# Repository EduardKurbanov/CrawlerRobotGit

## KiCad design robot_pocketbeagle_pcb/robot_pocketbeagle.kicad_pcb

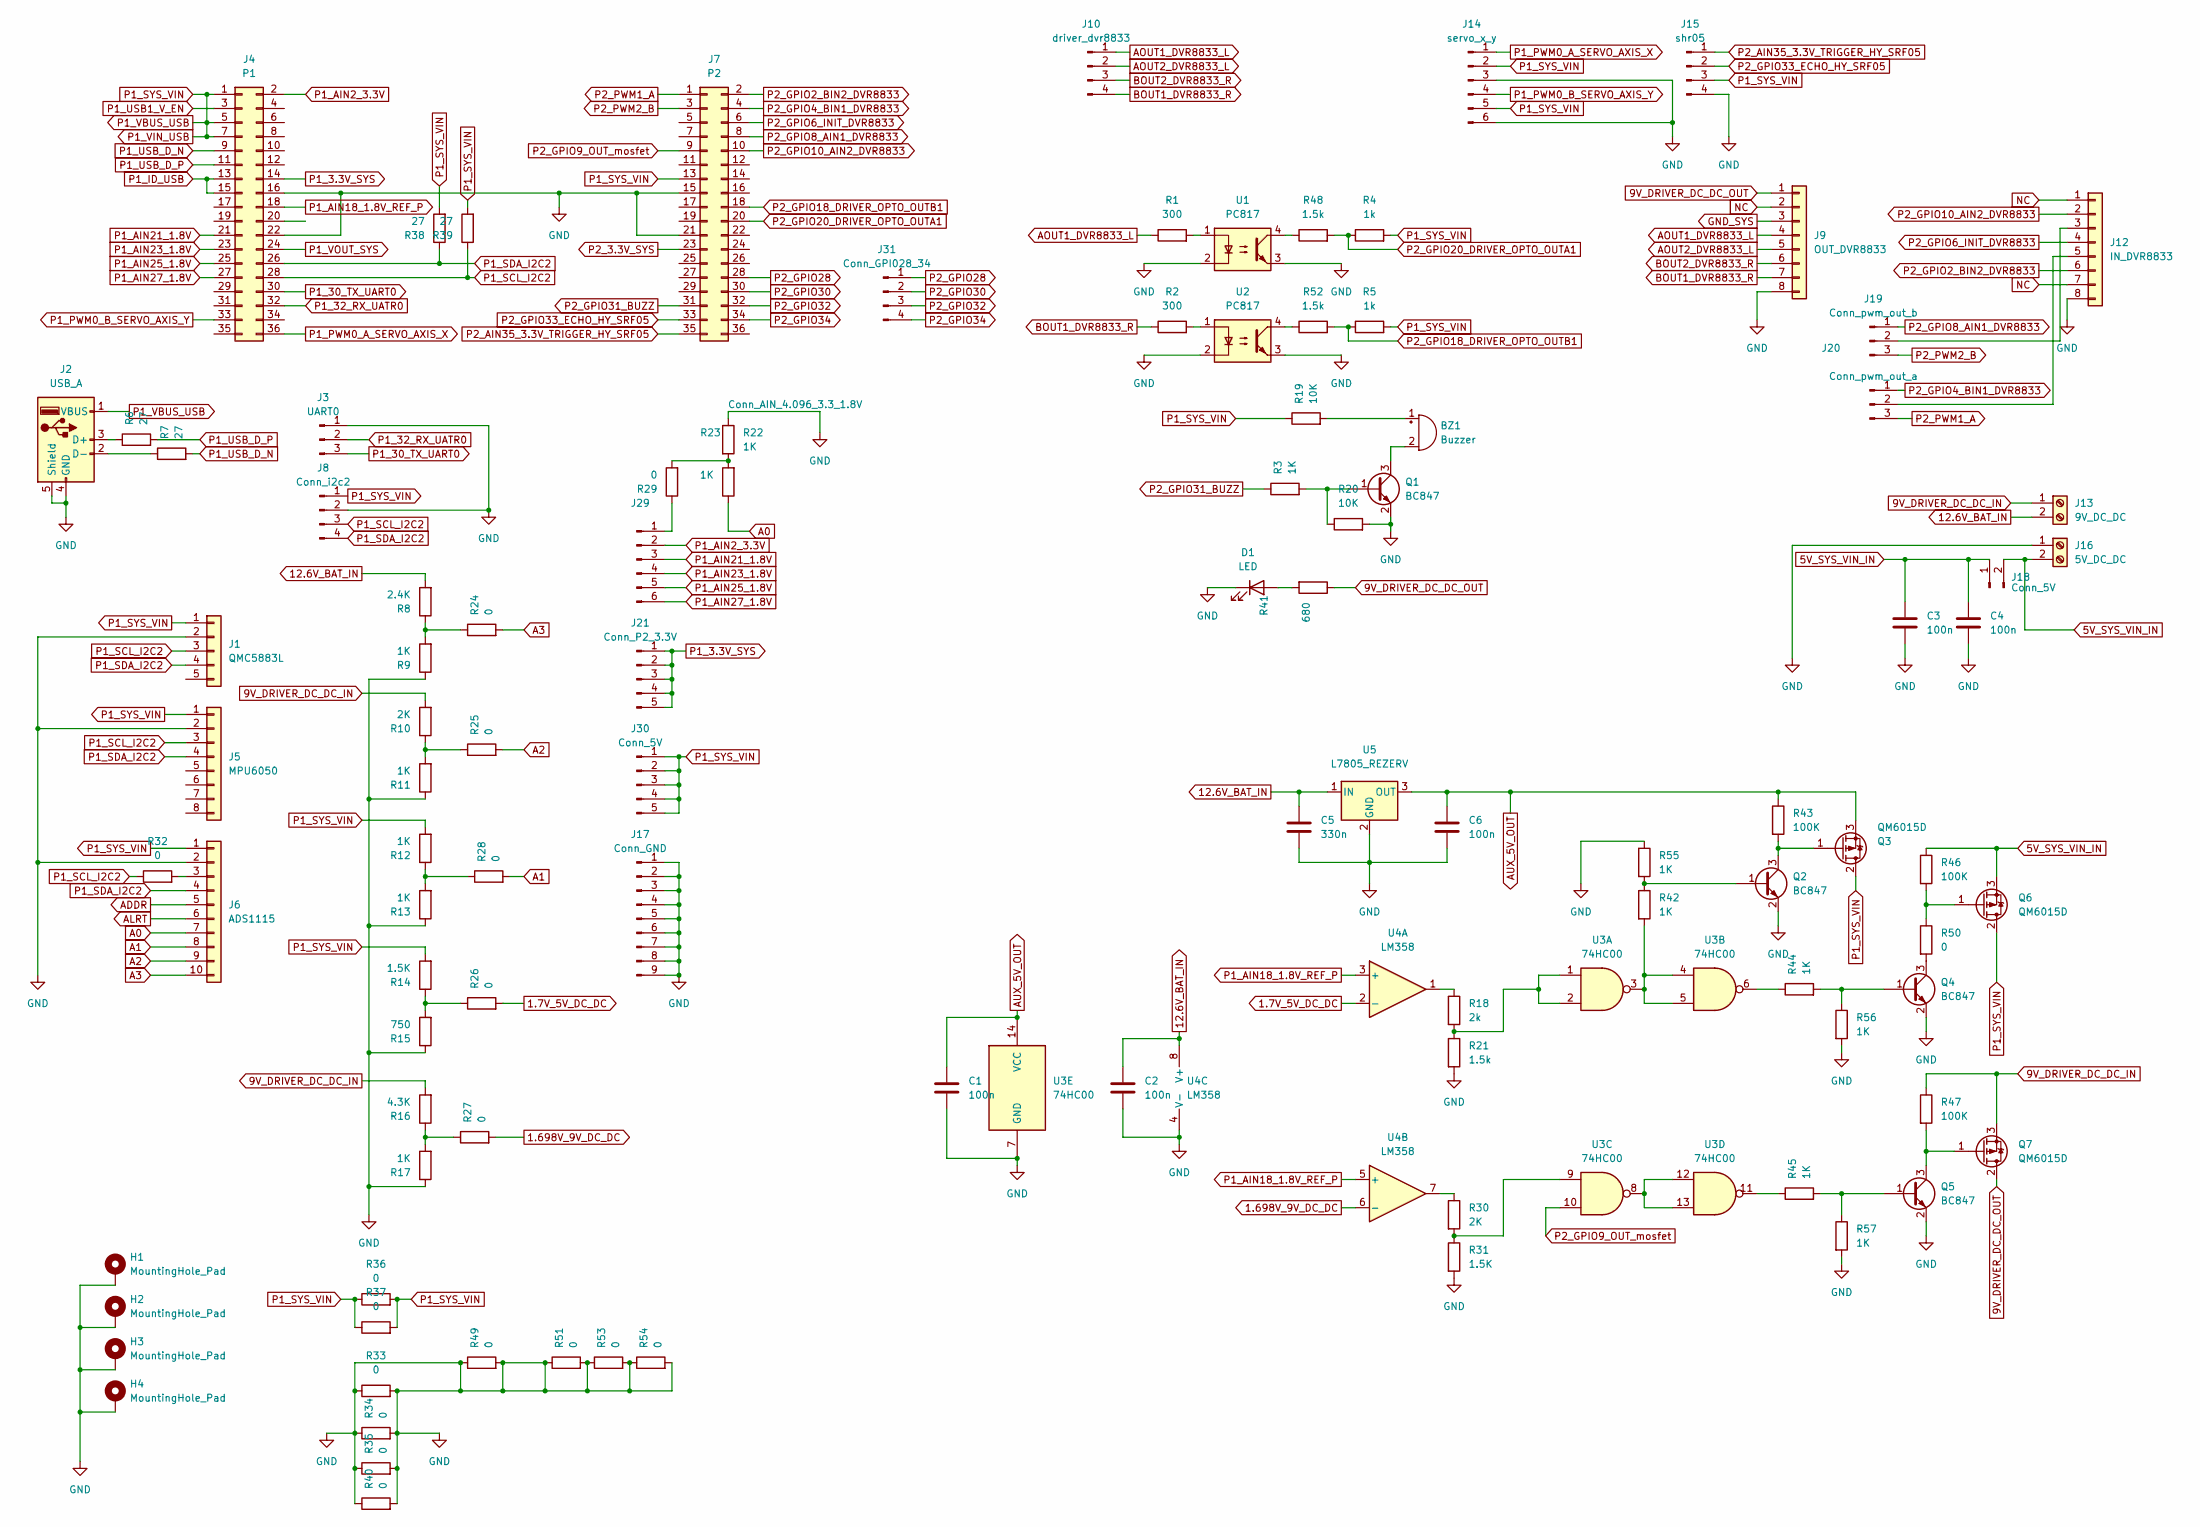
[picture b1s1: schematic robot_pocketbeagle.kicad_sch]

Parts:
BZ1: Buzzer; Buzzer_12x9.5RM7.6
C1, C2, C3, C4, C6: 100n; C_0805_2012Metric
C5: 330n; C_0805_2012Metric
D1: LED; LED_D3.0mm
H1, H2, H3, H4: MountingHole_Pad; MountingHole_3.2mm_M3_DIN965_Pad_TopBottom
J1: QMC5883L; PinSocket_1x05_P2.54mm_Vertical
J2: USB_A; USB_A_CONNFLY_DS1095-WNR0
J3: UART0; PinHeader_1x03_P2.54mm_Vertical
J4: P1; PinHeader_2x18_P2.54mm_Vertical
J5: MPU6050; PinHeader_1x08_P2.54mm_Vertical
J6: ADS1115; PinHeader_1x10_P2.54mm_Vertical
J7: P2; PinHeader_2x18_P2.54mm_Vertical
J8: Conn_i2c2; PinSocket_1x04_P2.54mm_Vertical
J9: OUT_DVR8833; PinSocket_1x08_P2.54mm_Vertical
J10: driver_dvr8833; PinHeader_1x04_P2.54mm_Vertical
J12: IN_DVR8833; PinSocket_1x08_P2.54mm_Vertical
J13: 9V_DC_DC; TerminalBlock_bornier-2_P5.08mm
J14: servo_x_y; PinHeader_1x06_P2.54mm_Vertical
J15: shr05; PinHeader_1x04_P2.54mm_Vertical
J16: 5V_DC_DC; TerminalBlock_bornier-2_P5.08mm
J17: Conn_GND; PinSocket_1x09_P2.54mm_Vertical
J18: Conn_5V; PinSocket_1x02_P2.54mm_Vertical
J19: Conn_pwm_out_b; PinSocket_1x03_P2.54mm_Vertical
J20: Conn_pwm_out_a; PinSocket_1x03_P2.54mm_Vertical
J21: Conn_P2_3.3V; PinSocket_1x05_P2.54mm_Vertical
J29: Conn_AIN_4.096_3.3_1.8V; PinSocket_1x06_P2.54mm_Vertical
J30: Conn_5V; PinSocket_1x05_P2.54mm_Vertical
J31: Conn_GPI028_34; PinSocket_1x04_P2.54mm_Vertical
Q1, Q2, Q4, Q5: BC847; SOT-23
Q3, Q6, Q7: QM6015D; TO-252-2
R1, R2: 300; R_0805_2012Metric
R3, R9, R11, R12, R13, R17, R22, R23, R42, R44, R45, R55, R56, R57: 1K; R_0805_2012Metric
R4, R5: 1k; R_0805_2012Metric
R6, R7, R38, R39: 27; R_0805_2012Metric
R8: 2.4K; R_0805_2012Metric
R10, R30: 2K; R_0805_2012Metric
R14, R31: 1.5K; R_0805_2012Metric
R15: 750; R_0805_2012Metric
R16: 4.3K; R_0805_2012Metric
R18: 2k; R_0805_2012Metric
R19, R20: 10K; R_0805_2012Metric
R21, R48, R52: 1.5k; R_0805_2012Metric
R24, R25, R26, R27, R28, R29, R49, R51: 0; R_0805_2012Metric
R32, R33, R34, R35, R36, R37, R40, R50, R53, R54: 0; R_1206_3216Metric
R41: 680; R_0805_2012Metric
R43, R46, R47: 100K; R_0805_2012Metric
U1, U2: PC817; DIP-4_W7.62mm
U3: 74HC00; SO-14_3.9x8.65mm_P1.27mm
U4: LM358; SO-8_3.9x4.9mm_P1.27mm
U5: L7805_REZERV; TO-252-2

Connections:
1.7V_5V_DC_DC: R26.2, U4.2 (-)
1.698V_9V_DC_DC: R27.2, U4.6 (-)
5V_SYS_VIN_IN: C3.1, C4.1, J16.2, J18.1, J18.2, Q6.3 (S), R46.1
9V_DRIVER_DC_DC_IN: J13.1, Q7.3 (S), R10.2, R16.2, R47.1
9V_DRIVER_DC_DC_OUT: J9.1, Q7.2 (D), R41.1
12.6V_BAT_IN: C2.1, C5.1, J13.2, R8.2, U4.8 (V+), U5.1 (IN)
A0: J6.7, R23.1
A1: J6.8, R28.2
A2: J6.9, R25.2
A3: J6.10, R24.2
ADDR: J6.5
ALRT: J6.6
AOUT1_DVR8833_L: J9.4, J10.1, R1.1
AOUT2_DVR8833_L: J9.5, J10.2
AUX_5V_OUT: C1.1, C6.1, Q3.3 (S), R43.1, U3.14 (VCC), U5.3 (OUT)
BOUT1_DVR8833_R: J9.7, J10.4, R2.1
BOUT2_DVR8833_R: J9.6, J10.3
GND: C1.2, C2.2, C3.2, C4.2, C5.2, C6.2, D1.1 (K), H1.1, H2.1, H3.1, H4.1, J1.2, J2.4 (GND), J2.5 (Shield), J3.1, J4.16, J4.22, J5.2, J6.2, J7.15, J7.21, J8.2, J9.8, J12.8, J14.3, J14.6, J15.4, J16.1, J17.1, J17.2, J17.3, J17.4, J17.5, J17.6, J17.7, J17.8, J17.9, Q1.2 (E), Q2.2 (E), Q4.2 (E), Q5.2 (E), R9.1, R11.1, R13.1, R15.1, R17.1, R20.2, R21.2, R22.1, R31.2, R33.1, R33.2, R34.1, R34.2, R35.1, R35.2, R40.1, R40.2, R49.1, R49.2, R51.1, R51.2, R53.1, R53.2, R54.1, R54.2, R55.1, R56.2, R57.2, U1.2, U1.3, U2.2, U2.3, U3.7 (GND), U4.4 (V-), U5.2 (GND)
GND_SYS: J9.3
NC: J9.2, J12.1, J12.7
unnamed: BZ1.1 (-), R19.2
unnamed: BZ1.2 (+), Q1.3 (C)
unnamed: D1.2 (A), R41.2
unnamed: J2.2 (D-), R7.1
unnamed: J2.3 (D+), R6.1
unnamed: J6.3, R32.2
unnamed: J12.3, J19.2
unnamed: J12.5, J20.2
unnamed: J29.1, R29.1
unnamed: Q1.1 (B), R3.2, R20.1
unnamed: Q2.1 (B), R42.1, R55.2
unnamed: Q2.3 (C), Q3.1 (G), R43.2
unnamed: Q4.1 (B), R44.2, R56.1
unnamed: Q4.3 (C), R50.2
unnamed: Q5.1 (B), R45.2, R57.1
unnamed: Q5.3 (C), Q7.1 (G), R47.2
unnamed: Q6.1 (G), R46.2, R50.1
unnamed: R1.2, U1.1
unnamed: R2.2, U2.1
unnamed: R10.1, R11.2, R25.1
unnamed: R12.1, R13.2, R28.1
unnamed: R14.1, R15.2, R26.1
unnamed: R16.1, R17.2, R27.1
unnamed: R18.1, U4.1
unnamed: R18.2, R21.1, U3.1, U3.2
unnamed: R22.2, R23.2, R29.2
unnamed: R8.1, R9.2, R24.1
unnamed: R30.1, U4.7
unnamed: R30.2, R31.1, U3.9
unnamed: R42.2, U3.3, U3.4, U3.5
unnamed: R44.1, U3.6
unnamed: R45.1, U3.11
unnamed: R48.1, U1.4
unnamed: R52.1, U2.4
unnamed: U3.8, U3.12, U3.13
P1_3.3V_SYS: J4.14, J21.1, J21.2, J21.3, J21.4, J21.5
P1_30_TX_UART0: J3.3, J4.30
P1_32_RX_UATR0: J3.2, J4.32
P1_AIN2_3.3V: J4.2, J29.2
P1_AIN18_1.8V_REF_P: J4.18, U4.3 (+), U4.5 (+)
P1_AIN21_1.8V: J4.21, J29.3
P1_AIN23_1.8V: J4.23, J29.4
P1_AIN25_1.8V: J4.25, J29.5
P1_AIN27_1.8V: J4.27, J29.6
P1_ID_USB: J4.13, J4.15
P1_PWM0_A_SERVO_AXIS_X: J4.36, J14.1
P1_PWM0_B_SERVO_AXIS_Y: J4.33, J14.4
P1_SCL_I2C2: J1.3, J4.28, J5.3, J8.3, R32.1, R39.1
P1_SDA_I2C2: J1.4, J4.26, J5.4, J6.4, J8.4, R38.1
P1_SYS_VIN: J1.1, J2.1 (VBUS), J4.1, J4.5, J4.7, J5.1, J6.1, J7.13, J8.1, J14.2, J14.5, J15.3, J30.1, J30.2, J30.3, J30.4, J30.5, Q3.2 (D), Q6.2 (D), R4.2, R5.2, R12.2, R14.2, R19.1, R36.1, R36.2, R37.1, R37.2, R38.2, R39.2
P1_USB1_V_EN: J4.3
P1_USB_D_N: J4.9, R7.2
P1_USB_D_P: J4.11, R6.2
P1_VOUT_SYS: J4.24
P2_3.3V_SYS: J7.23
P2_AIN35_3.3V_TRIGGER_HY_SRF05: J7.35, J15.1
P2_GPIO2_BIN2_DVR8833: J7.2, J12.6
P2_GPIO4_BIN1_DVR8833: J7.4, J20.1
P2_GPIO6_INIT_DVR8833: J7.6, J12.4
P2_GPIO8_AIN1_DVR8833: J7.8, J19.1
P2_GPIO9_OUT_mosfet: J7.9, U3.10
P2_GPIO10_AIN2_DVR8833: J7.10, J12.2
P2_GPIO18_DRIVER_OPTO_OUTB1: J7.18, R5.1, R52.2
P2_GPIO20_DRIVER_OPTO_OUTA1: J7.20, R4.1, R48.2
P2_GPIO28: J7.28, J31.1
P2_GPIO30: J7.30, J31.2
P2_GPIO31_BUZZ: J7.31, R3.1
P2_GPIO32: J7.32, J31.3
P2_GPIO33_ECHO_HY_SRF05: J7.33, J15.2
P2_GPIO34: J7.34, J31.4
P2_PWM1_A: J7.1, J20.3
P2_PWM2_B: J7.3, J19.3

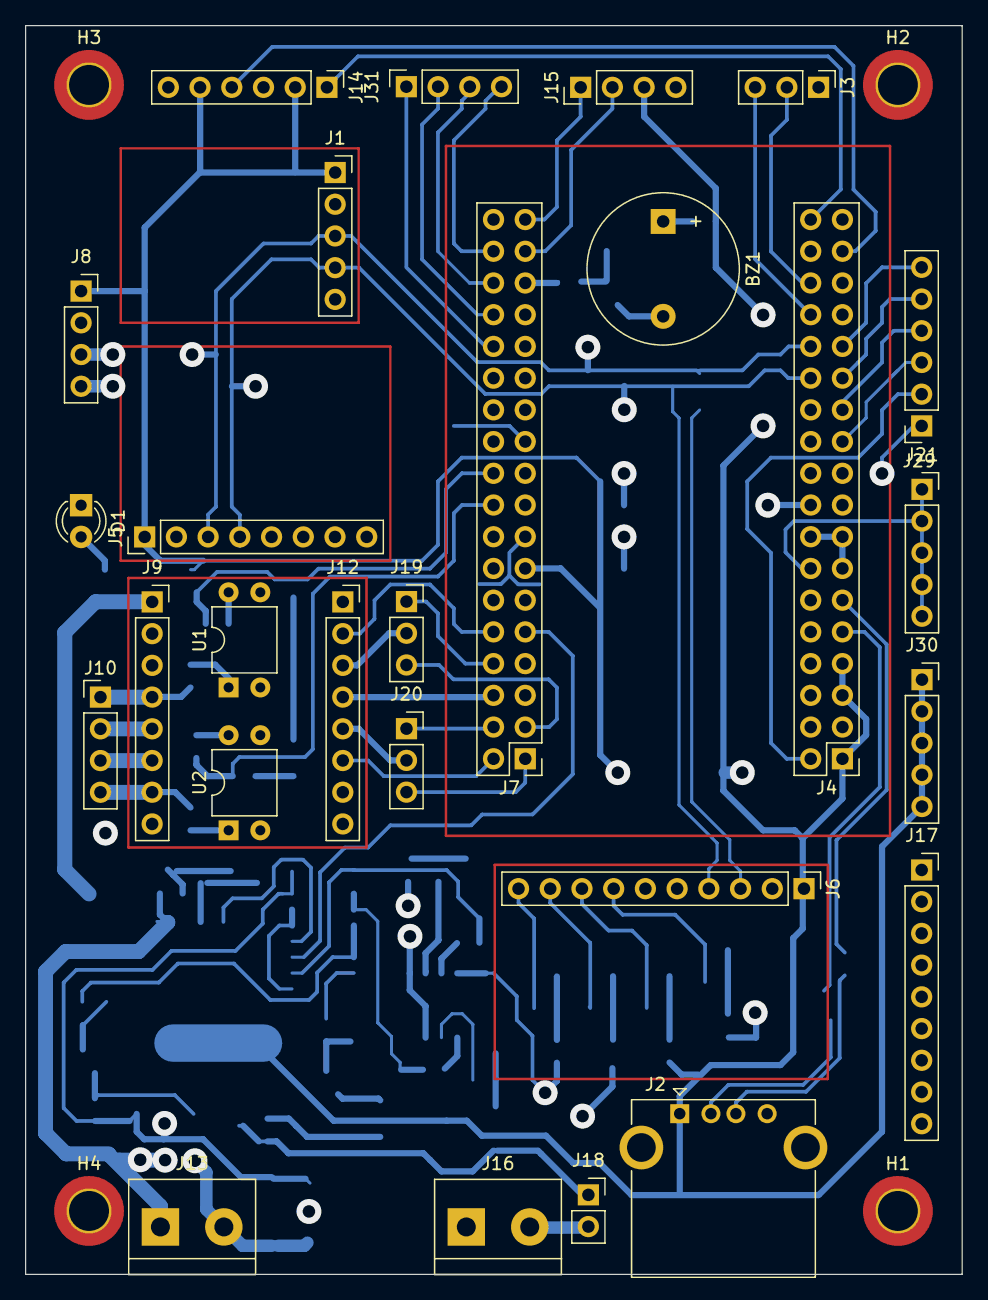
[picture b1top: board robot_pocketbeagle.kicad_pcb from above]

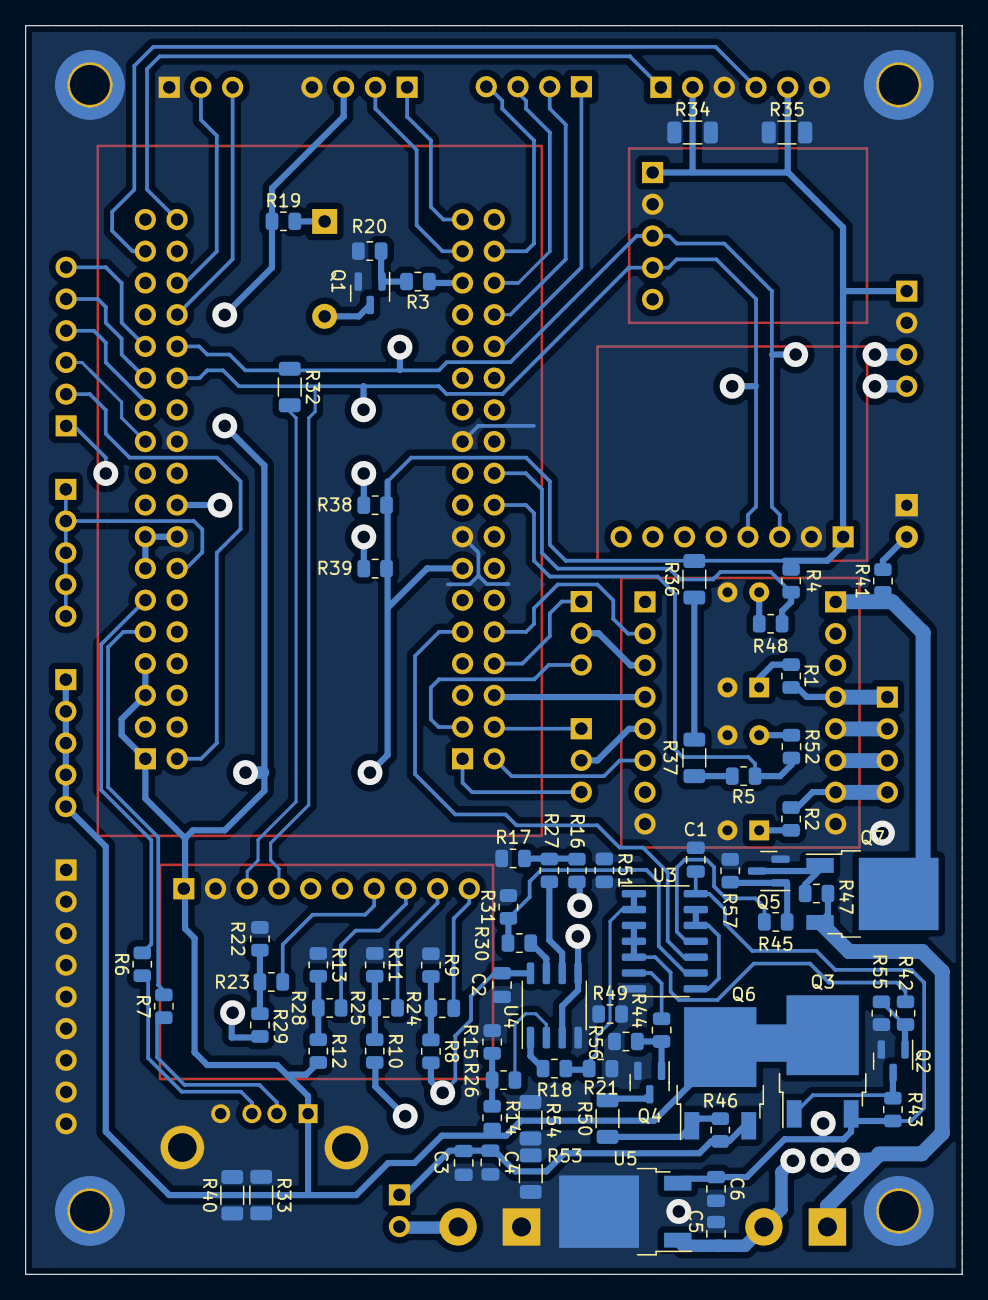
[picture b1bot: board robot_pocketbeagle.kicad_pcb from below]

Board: 2 copper layers, 75.0 x 100.0 mm, 104 parts (73 on the bottom side), 86 nets.

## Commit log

2023-12-03 alpa version robot
2023-12-03 fix error
2023-12-03 fix error2
2023-12-03 add jpg
2023-12-03 fix def driver motor
2023-12-03 fix doc def motor driver
2023-12-03 fix doc def sonar
2023-12-06 add def gyroscope_accelerometer_robot():
2023-12-06 fix code def gyroscope_accelerometer_robot():
2023-12-08 adding explanation to registers to mpu6050
2023-12-08 changing registers in mpu6050
2023-12-09 add axix_rotation_angle_x, axix_rotation_angle_y (mpu6050)
2023-12-09 fix doc mpu6050
2023-12-09 mpu6050 moved to a separate class
2023-12-10 fix sintas
2023-12-10 fix sintax.
2023-12-10 add class hmc5883l
2023-12-12 add sensor qmc5883l
2023-12-13 fix tegister bit and add def axis_x_y_z
2023-12-14 fix 1
2023-12-14 code optimization mpu6050
2023-12-15 fix sitax
2023-12-16 fix code
2023-12-17 add doc
2023-12-17 add doc drv8833
2023-12-20 add datasheet pocketbeagle
2023-12-20 add discharge_controller
2023-12-24 correcting syntax errors and breaking classes into separate blocks
2023-12-24 add in main import
2023-12-25 update ads1115
2023-12-29 fix bag ads1115
2023-12-29 add driver_motor_pwm_dvr8833
2023-12-30 fix cod erorrs
2023-12-30 fix code erorrs
2023-12-31 optimization code sg90
2024-01-02 fix bag
2024-01-02 fix servo
2024-01-02 add doc ino219
2024-01-02 add class ino219
2024-01-09 add pcb
2024-01-09 add class alert
2024-01-12 update pcb
2024-01-12 add new doc
2024-01-12 add board
2024-01-13 add sim. shem and fix board shem
2024-01-13 fix board
2024-01-14 fix board optopara
2024-01-18 board debugging
2024-01-18 board debugging 1
2024-01-18 board debugging 2
2024-01-20 board debugging 3
2024-01-20 board debugging 4
2024-01-30 fix metod get_axix_x_y_z
2024-01-30 add fun
2024-01-31 update qmc5883l
2024-02-02 add doc and fix shem board
